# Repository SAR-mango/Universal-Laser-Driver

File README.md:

# Universal Laser Driver
Solves the problem of having to match batteries, laser drivers, and diodes based on input and output voltage and current requirements.

## Applications
Intended for low-power laser pointers where space is minimal.

Especially well suited for builds utilizing the Leadlight Pen Host, because the PCB is designed to fit in the plastic carrier that normally holds the switch board. The Leadlight Pen Host requires two 10440-sized battery cells, and the Universal Laser Driver allows the user to swap between AAA alkaline and 10440 Li-ion cells without worrying about damaging the driver or not having sufficient voltage to power the diode.

## Specifications
Vin: 2.25–9V

Vout: 1–7V

Iout: 0–200mA

These can very significantly. Lower Vin and/or higher Vout (due to the nonlinear nature of laser diodes) would result in a lower maximum Iout. A lower Iout setting would extend the Vin and Vout ranges.

## Project Updates
**July 2023**: The test board has been shown to reliably produce stable currents between 0 and 200mA using a test load with six standard silicon diodes and one 1Ω resistor in series. Minimal noise was found in the output current waveform, especially below 20MHz. Noise pulses were no more than several nanoseconds long. Therefore, the Universal Laser Driver is unlikely to cause damage or reduced reliability to even the most delicate laser diodes.

The version of the driver meant for the Leadlight Pen Host will be updated to reflect the current schematic for the test board.

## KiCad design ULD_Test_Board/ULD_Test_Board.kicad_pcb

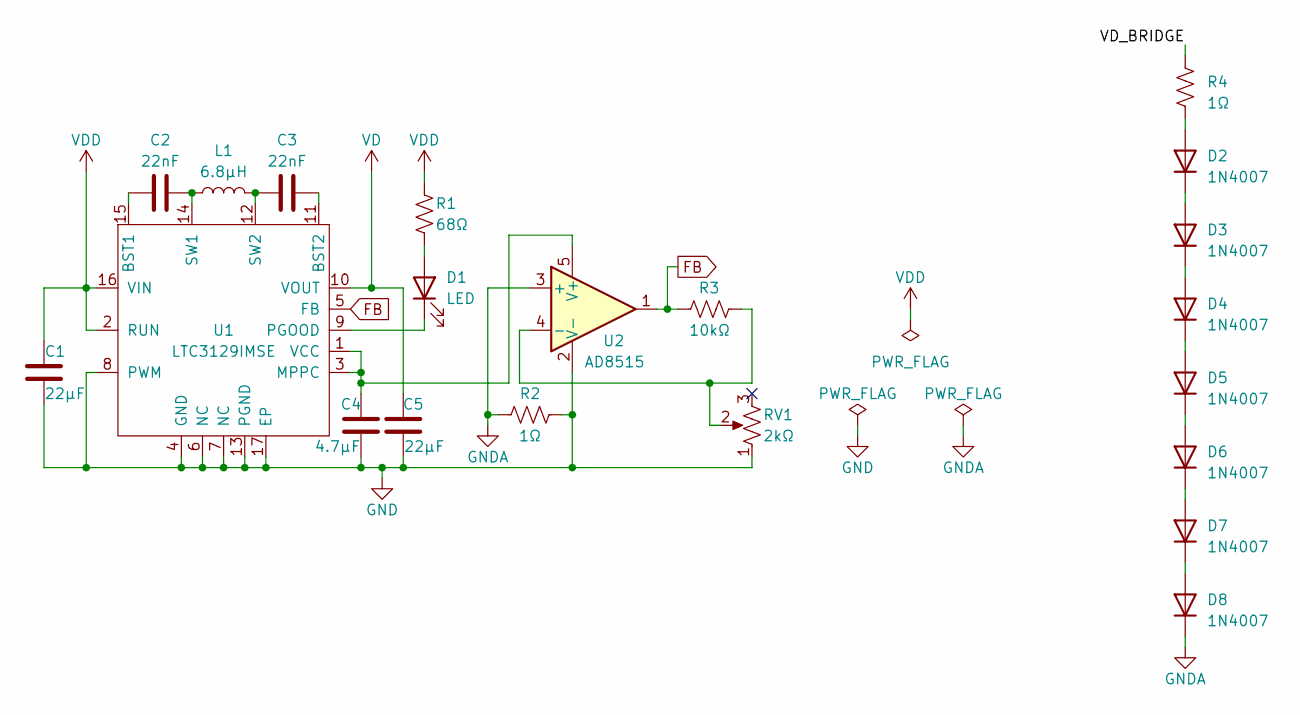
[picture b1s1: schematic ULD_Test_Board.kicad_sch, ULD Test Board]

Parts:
C1, C5: 22µF; C_1210_3225Metric_Pad1.33x2.70mm_HandSolder
C2, C3: 22nF; C_0805_2012Metric_Pad1.18x1.45mm_HandSolder
C4: 4.7µF; C_1210_3225Metric_Pad1.33x2.70mm_HandSolder
D1: LED; LED_0805_2012Metric_Pad1.15x1.40mm_HandSolder
D2, D3, D4, D5, D6, D7, D8: 1N4007; D_SOD-123F
L1: 6.8µH; L_Taiyo-Yuden_MD-4040
R1: 68Ω; R_0805_2012Metric_Pad1.20x1.40mm_HandSolder
R2, R4: 1Ω; R_1210_3225Metric_Pad1.30x2.65mm_HandSolder
R3: 10kΩ; R_0805_2012Metric_Pad1.20x1.40mm_HandSolder
RV1: 2kΩ; Potentiometer_Bourns_TC33X_Vertical
U1: LTC3129IMSE; MSOP-16-1EP_3x4.039mm_P0.5mm_EP1.651x2.845mm
U2: AD8515; SOT-23-5_HandSoldering

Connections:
/VD_BRIDGE: R4.1
FB: R3.2, U1.5 (FB), U2.1
GND: C1.2, C4.2, C5.1, R2.2, RV1.1, U1.4 (GND), U1.6 (NC), U1.7 (NC), U1.8 (PWM), U1.13 (PGND), U1.17 (EP), U2.2 (V-)
GNDA: D8.1 (K), R2.1, U2.3 (+)
unnamed: D1.2 (A), R1.2
unnamed: D1.1 (K), U1.9 (PGOOD)
unnamed: D2.2 (A), R4.2
unnamed: D2.1 (K), D3.2 (A)
unnamed: D3.1 (K), D4.2 (A)
unnamed: D4.1 (K), D5.2 (A)
unnamed: D5.1 (K), D6.2 (A)
unnamed: D6.1 (K), D7.2 (A)
unnamed: D7.1 (K), D8.2 (A)
unnamed: C2.1, U1.15 (BST1)
unnamed: C3.2, U1.11 (BST2)
unnamed: C4.1, U1.1 (VCC), U1.3 (MPPC), U2.5 (V+)
unnamed: C2.2, L1.1, U1.14 (SW1)
unnamed: C3.1, L1.2, U1.12 (SW2)
unnamed: R3.1, RV1.2, U2.4 (-)
VD: C5.2, U1.10 (VOUT)
VDD: C1.1, R1.1, U1.2 (RUN), U1.16 (VIN)

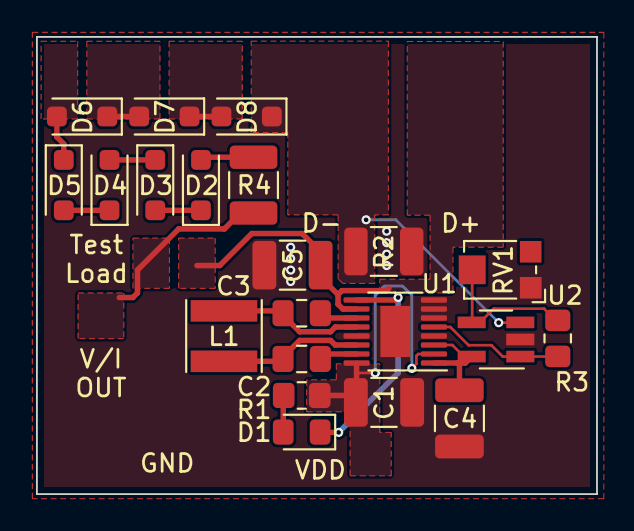
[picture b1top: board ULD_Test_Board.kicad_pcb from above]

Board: 2 copper layers, 31.1 x 25.4 mm, 21 parts (0 on the bottom side), 20 nets.

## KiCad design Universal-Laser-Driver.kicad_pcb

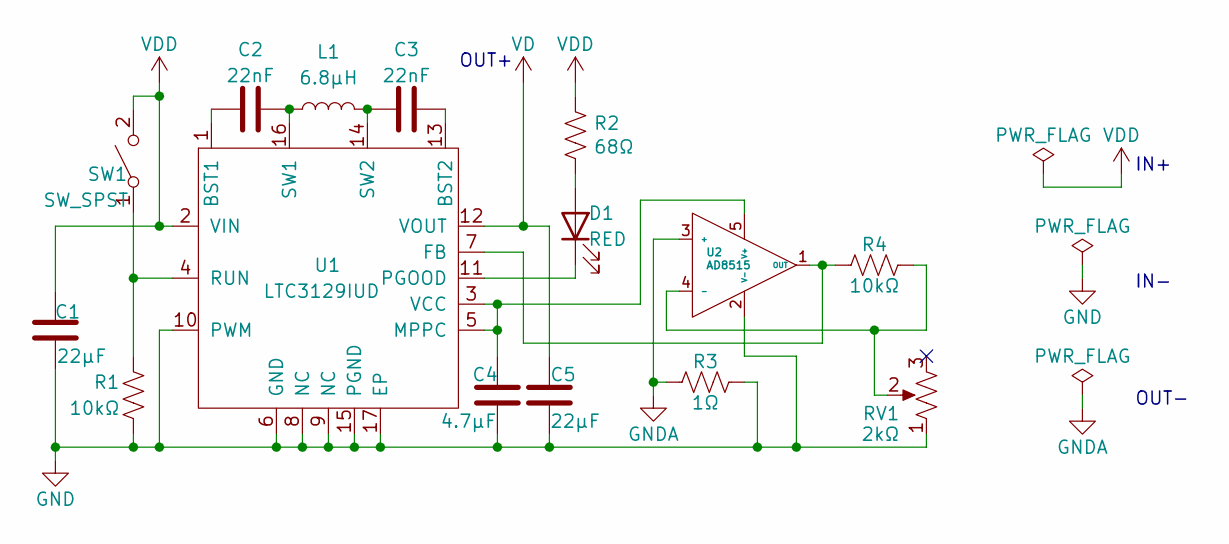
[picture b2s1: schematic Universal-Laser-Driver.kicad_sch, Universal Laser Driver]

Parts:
C1, C5: 22µF; C_0603_1608Metric; MPN CL10A226MO7JZNC
C2, C3: 22nF; C_0402_1005Metric; MPN C1005X7R1E223K050BB
C4: 4.7µF; C_0402_1005Metric; MPN CL05A475MP5NRNC
D1: RED; LED_0402_1005Metric; MPN 5988A10107F
L1: 6.8µH; L_Taiyo-Yuden_MD-4040; MPN LQH44PH6R8MPRL
R1, R4: 10kΩ; R_0402_1005Metric; MPN ERJ-PA2F1002X
R2: 68Ω; R_0402_1005Metric; MPN ERJ-U02J680X
R3: 1Ω; R_0402_1005Metric; MPN MCS0402MC1008FE000
RV1: 2kΩ; Potentiometer_Bourns_TC33X_Vertical; MPN TC33X-2-202E
SW1: SW_SPST; WUERTH_434121050836; MPN 434121050836
U1: LTC3129IUD; VQFN-16-1EP_3x3mm_P0.5mm_EP1.68x1.68mm; MPN LTC3129IUD
U2: AD8515; SOT-353_SC-70-5; MPN AD8515AKS-REEL7

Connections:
GND: C1.1, C4.2, C5.2, R1.2, R3.1, RV1.1, U1.6 (GND), U1.8 (NC), U1.9 (NC), U1.10 (PWM), U1.15 (PGND), U1.17 (EP), U2.2 (V-)
GNDA: R3.2, U2.3 (+)
unnamed: C2.1, L1.1, U1.16 (SW1)
unnamed: C2.2, U1.1 (BST1)
unnamed: C3.1, U1.13 (BST2)
unnamed: C3.2, L1.2, U1.14 (SW2)
unnamed: C4.1, U1.3 (VCC), U1.5 (MPPC), U2.5 (V+)
unnamed: D1.1 (K), U1.11 (PGOOD)
unnamed: D1.2 (A), R2.2
unnamed: R1.1, SW1.1 (A), U1.4 (RUN)
unnamed: R4.1, RV1.2, U2.4 (-)
unnamed: R4.2, U1.7 (FB), U2.1 (OUT)
VD: C5.1, U1.12 (VOUT)
VDD: C1.2, R2.1, SW1.2 (B), U1.2 (VIN)

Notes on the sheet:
IN-
IN+
OUT-
OUT+

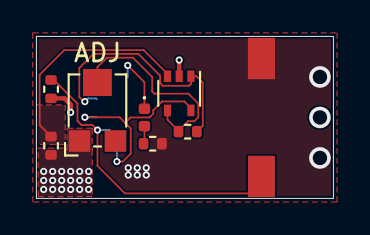
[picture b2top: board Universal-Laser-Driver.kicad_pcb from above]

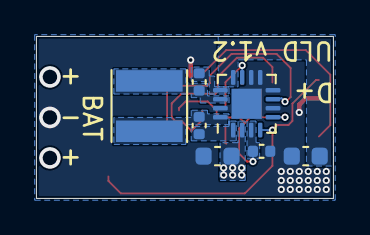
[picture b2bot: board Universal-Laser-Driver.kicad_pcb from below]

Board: 2 copper layers, 16.5 x 9.0 mm, 15 parts (7 on the bottom side), 14 nets.

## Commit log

2021-09-14 Added all project files
2021-09-26 Removed unnecessary rescue files
2021-09-26 Minor changes for clarity
2021-11-07 Fixed mislabeled net in schematic
2022-04-12 Updated to KiCAD 6
2022-04-12 Updated .gitignore
2022-06-07 Updated gitignore
2022-06-07 Removed extra backups
2022-06-07 Created Universal-Laser-Driver-2022-06-07_112458.zip
2022-06-08 Updated schematic PDF
2023-06-09 add test board project folder/files
